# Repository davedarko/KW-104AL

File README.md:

# KW-104AL Eagle Library
Display library, controller board based on 74hc595 and breakout board for breadboards.
Works also with KW-105AL, since it has the same footprint. 
Use standard 1.27mm / 0.05" pin headers for the pins.

See http://hackaday.io/page/760 for more details.

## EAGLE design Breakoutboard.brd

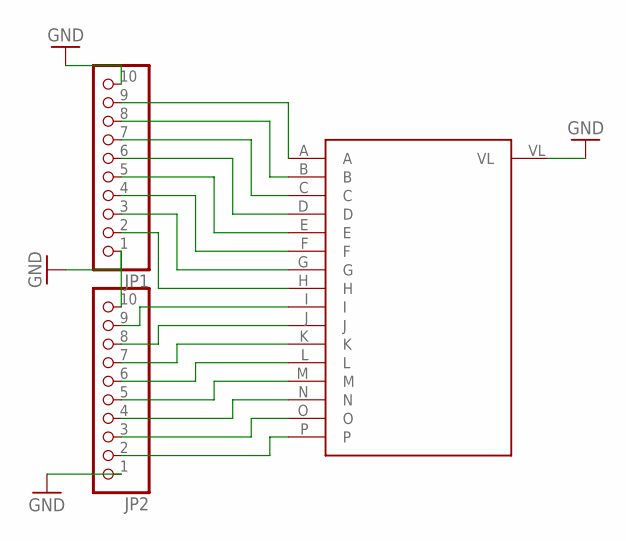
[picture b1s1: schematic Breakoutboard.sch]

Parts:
JP1, JP2: PINHD-1X10; 1X10
U$1: 1.27KW-104AL; 127

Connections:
GND: JP1.1, JP1.10, JP2.1, JP2.10, U$1.VL
unnamed: JP1.9, U$1.A
unnamed: JP1.8, U$1.B
unnamed: JP1.7, U$1.C
unnamed: JP1.6, U$1.D
unnamed: JP1.5, U$1.E
unnamed: JP1.4, U$1.F
unnamed: JP1.3, U$1.G
unnamed: JP1.2, U$1.H
unnamed: JP2.9, U$1.I
unnamed: JP2.8, U$1.J
unnamed: JP2.7, U$1.K
unnamed: JP2.6, U$1.L
unnamed: JP2.5, U$1.M
unnamed: JP2.4, U$1.N
unnamed: JP2.3, U$1.O
unnamed: JP2.2, U$1.P

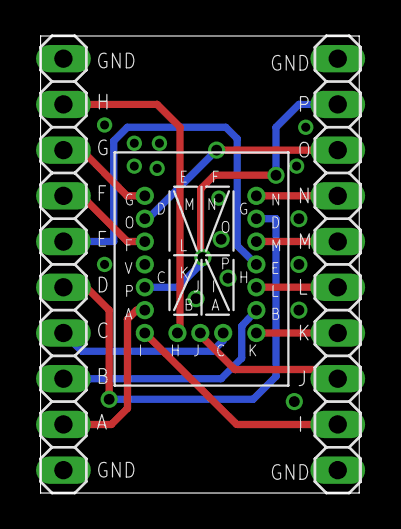
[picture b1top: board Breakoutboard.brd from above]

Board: 2 copper layers, 17.7 x 25.4 mm, 3 parts (0 on the bottom side), 17 nets.

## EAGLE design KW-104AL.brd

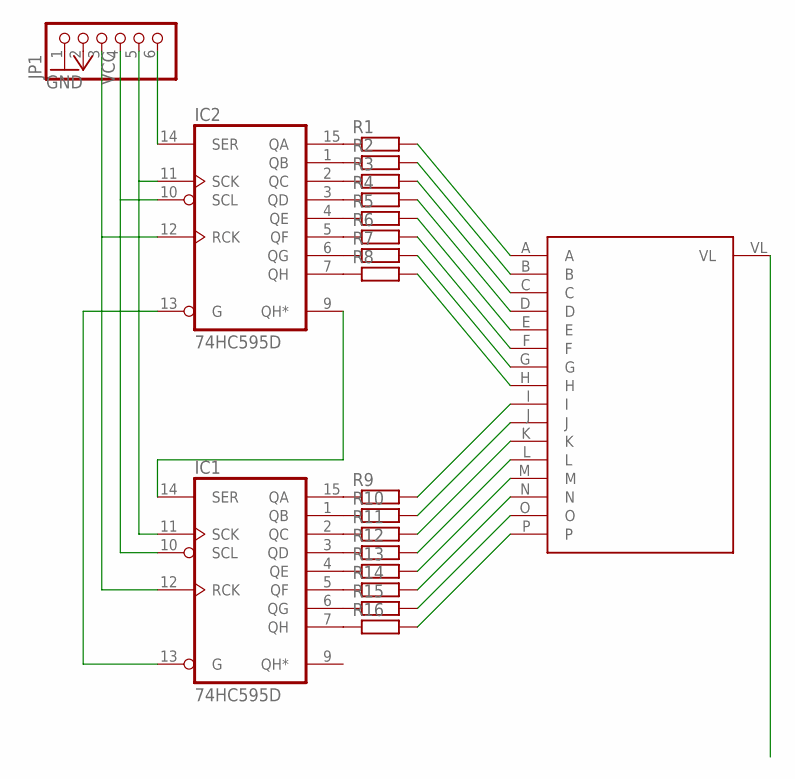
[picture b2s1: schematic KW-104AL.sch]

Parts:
IC1, IC2: 74HC595D; SO16
JP1: PINHD-1X6CB; 1X06-CLEANBIG
R1, R2, R3, R4, R5, R6, R7, R8, R9, R10, R11, R12, R13, R14, R15, R16: R-EU_R0402; R0402
U$1: 1.27KW-104AL; 127

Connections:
GND: IC1.8 (GND), IC2.8 (GND), JP1.1
unnamed: IC1.14 (SER), IC2.9 (QH*)
unnamed: IC1.11 (SCK), IC2.11 (SCK), JP1.5
unnamed: IC1.10 (SCL), IC2.10 (SCL), JP1.4
unnamed: IC1.12 (RCK), IC2.12 (RCK), JP1.3
unnamed: IC1.13 (G), IC2.13 (G)
unnamed: IC2.15 (QA), R1.1
unnamed: IC2.1 (QB), R2.1
unnamed: IC2.2 (QC), R3.1
unnamed: IC2.3 (QD), R4.1
unnamed: IC2.4 (QE), R5.1
unnamed: IC2.5 (QF), R6.1
unnamed: IC2.6 (QG), R7.1
unnamed: IC2.7 (QH), R8.1
unnamed: IC1.15 (QA), R9.1
unnamed: IC1.1 (QB), R10.1
unnamed: IC1.2 (QC), R11.1
unnamed: IC1.3 (QD), R12.1
unnamed: IC1.4 (QE), R13.1
unnamed: IC1.5 (QF), R14.1
unnamed: IC1.6 (QG), R15.1
unnamed: IC1.7 (QH), R16.1
unnamed: R1.2, U$1.A
unnamed: R2.2, U$1.B
unnamed: R3.2, U$1.C
unnamed: R4.2, U$1.D
unnamed: R5.2, U$1.E
unnamed: R6.2, U$1.F
unnamed: R7.2, U$1.G
unnamed: R8.2, U$1.H
unnamed: R9.2, U$1.I
unnamed: R10.2, U$1.J
unnamed: R11.2, U$1.K
unnamed: R12.2, U$1.L
unnamed: R13.2, U$1.M
unnamed: R14.2, U$1.N
unnamed: R15.2, U$1.O
unnamed: R16.2, U$1.P
unnamed: IC2.14 (SER), JP1.6
VCC: IC1.16 (VCC), IC2.16 (VCC), JP1.2

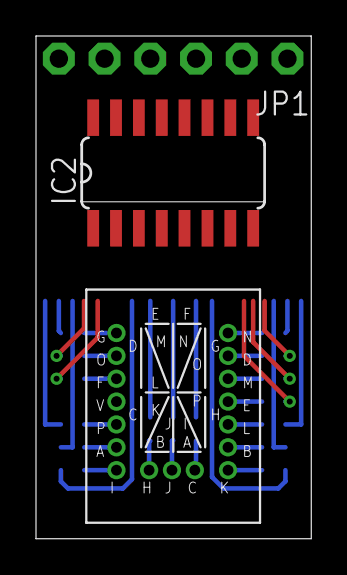
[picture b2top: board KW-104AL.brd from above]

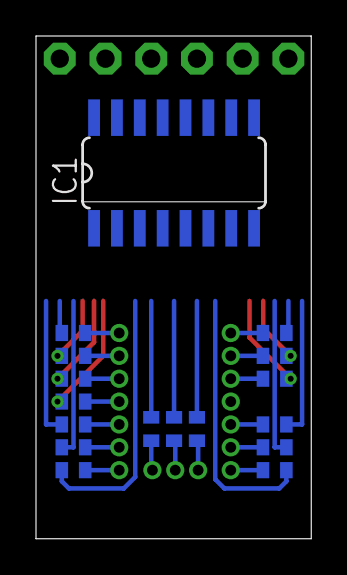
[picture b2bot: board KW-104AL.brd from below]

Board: 2 copper layers, 15.3 x 27.9 mm, 20 parts (17 on the bottom side), 40 nets.

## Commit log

2015-02-18 publish
2015-02-18 created readme.md
2015-02-18 edited readme
2015-02-18 gitignore, not centered breakoutboard fixed
2015-02-18 upsies
2015-02-18 deleted backups
2015-02-18 added description to pins
2015-02-18 wasn't quite centered yet
